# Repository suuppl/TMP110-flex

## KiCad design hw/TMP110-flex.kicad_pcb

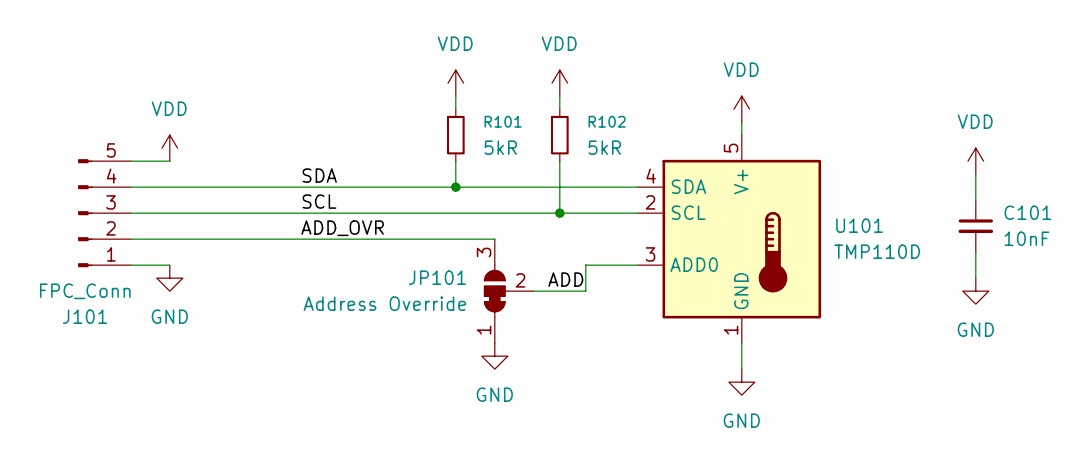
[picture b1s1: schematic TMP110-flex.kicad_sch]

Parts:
C101: 10nF; C_0201_0603Metric
J101: FPC_Conn; Conn_FCC_05_P0.5mm
JP101: Address Override; SolderJumper-3_P1.3mm_Bridged12_RoundedPad1.0x1.5mm
R101, R102: 5kR; R_0201_0603Metric
U101: TMP110D; Texas_X2SON-5_0.8x0.8mm_P0.48mm

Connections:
/ADD: JP101.2 (C), U101.3 (ADD0)
/ADD_OVR: J101.2, JP101.3 (B)
/SCL: J101.3, R102.2, U101.2 (SCL)
/SDA: J101.4, R101.2, U101.4 (SDA)
GND: C101.2, J101.1, JP101.1 (A), U101.1 (GND)
VDD: C101.1, J101.5, R101.1, R102.1, U101.5 (V+)

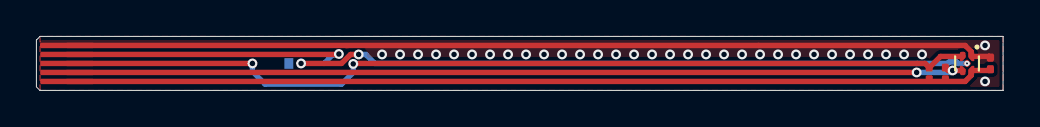
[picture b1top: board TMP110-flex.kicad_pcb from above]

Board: 2 copper layers, 53.7 x 3.0 mm, 6 parts (1 on the bottom side), 6 nets.
